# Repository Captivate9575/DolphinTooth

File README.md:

# DolphinTooth
Passthrough the official Wii bluetooth module into Dolphin.

All files free to use, thank you to C0rn3j for the initial documentation of the bluetooth module test pads, I have probed the mezzanine connector to get the pinout for that.

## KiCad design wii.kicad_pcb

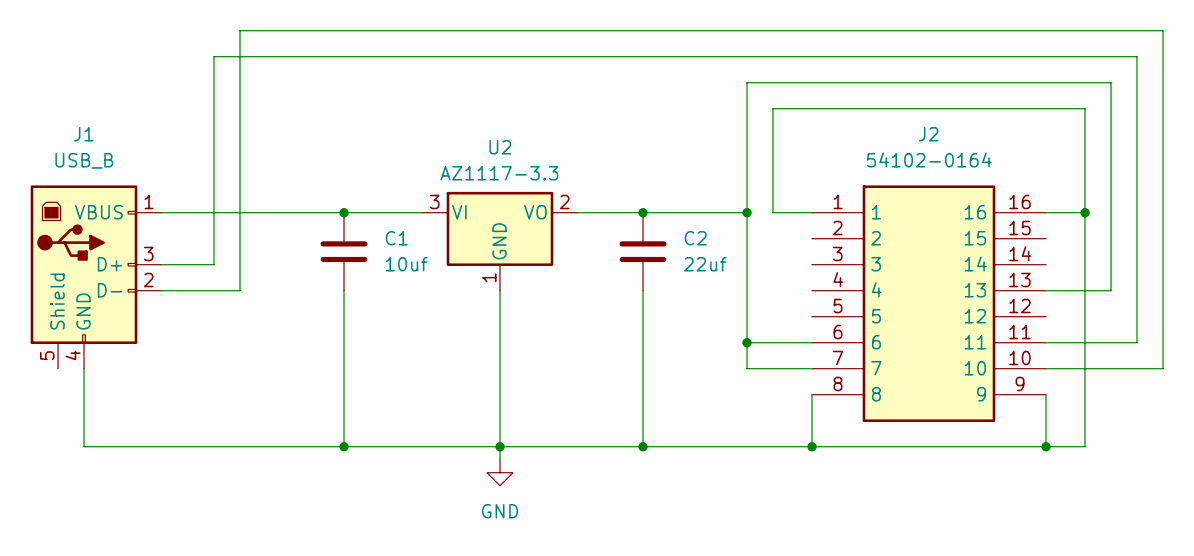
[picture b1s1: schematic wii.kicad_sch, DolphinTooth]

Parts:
C1: 10uf; C_1206_3216Metric
C2: 22uf; C_1206_3216Metric
J1: USB_B; USB_B_OST_USB-B1HSxx_Horizontal
J2: 54102-0164; 541020164; Mouser Part Number 538-54102-0164
U2: AZ1117-3.3; SOT-223-3_TabPin2

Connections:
GND: C1.2, C2.2, J1.4 (GND), J2.1, J2.8, J2.9, J2.16, U2.1 (GND)
unnamed: J1.3 (D+), J2.11
unnamed: J1.2 (D-), J2.10
unnamed: C1.1, J1.1 (VBUS), U2.3 (VI)
unnamed: C2.1, J2.6, J2.7, J2.13, U2.2 (VO)

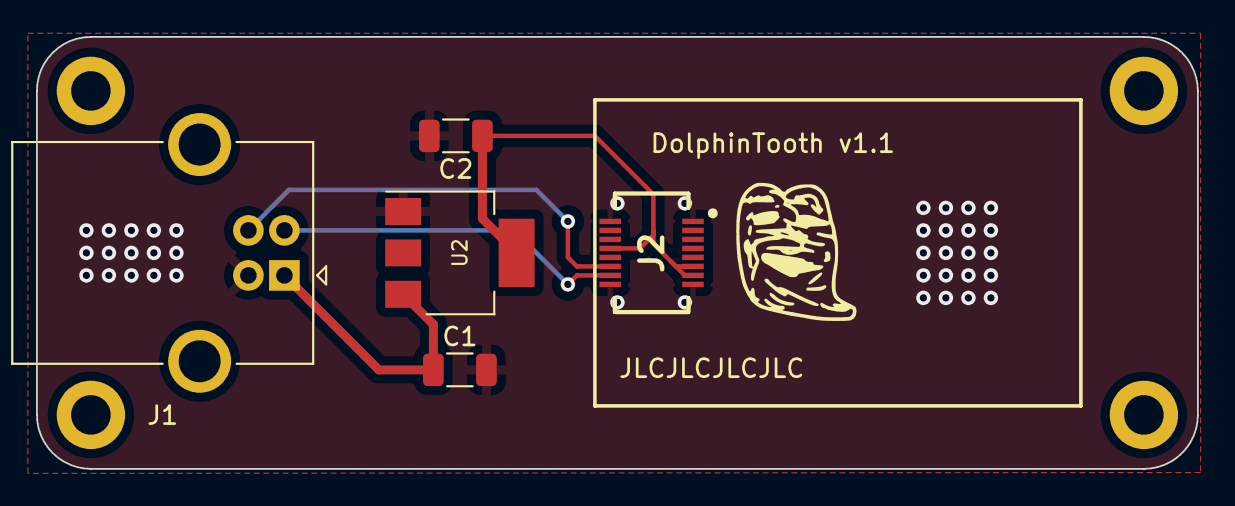
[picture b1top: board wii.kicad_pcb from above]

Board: 2 copper layers, 64.5 x 24.0 mm, 5 parts (0 on the bottom side), 5 nets.

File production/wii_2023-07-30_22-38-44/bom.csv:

Designator,Footprint,Quantity,Value,LCSC Part #
C1,1206,1,10uf,
C2,1206,1,22uf,
J1,USB_B_OST_USB-B1HSxx_Horizontal,1,USB_B,
J2,541020164,1,54102-0164,
U2,SOT-223-3_TabPin2,1,AZ1117-3.3,

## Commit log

2023-07-05 Version 1
2023-07-05 Images
2023-07-30 change to usb b
    also added html bom plugin and removed round tracks
